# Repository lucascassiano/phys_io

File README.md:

# phys_io
Opensource Low cost hand|finger tracking device for HCIs and Physiotherapy applications

## Possible ICs
### Capacitive Touch/Proximity ICs
- MPR121 - 12Channel w/ I2C interf - https://www.adafruit.com/product/1982

### Power Supply

- TP4056 - LiPo Charger - https://www.sparkfun.com/products/10217

- UA78M33 - 3.3v Regulator

### Micro Controller

- ATMega32u4 - (maybe it's too much for a simple application)

- Attiny44 

## Software - API / Viz tool

- Node.js 
- Babylon.js
- Unity (?)

## Components to buy - April 2017
| Component     | Price (US$) |Quantity| link
| ------------- |:------:|:-----:| --------- |
| TP4056 Battery Charge |  1.65  | 10 | [dx](http://www.dx.com/p/tp4056-4-2w-1-2a-5v-lithium-battery-charging-discharging-protection-module-w-micro-usb-blue-397213#.WOpxGlLlQU4)|
| MPR121 Breakout I2C   |  4.99  | 10 | [dx](http://www.dx.com/p/mpr121-breakout-i2c-capacitive-touch-sensor-controller-module-for-arduino-raspberry-pi-382663#.WOpyglLlSAw)|
| Arduino Micro Pro     |  5.99  | 10 | [dx](http://www.dx.com/p/open-smart-atmega32u4-development-board-pro-micro-for-arduino-452853#.WOpy3lLlSAw)|
| HC-06 Bluetooth Module|  5.99  | 10 | [dx](http://www.dx.com/p/hc-06-serial-port-passthrough-wireless-slave-transceiver-bluetooth-module-for-arduino-382686#.WOpzOFLlSAw)|
| 5x lipo Battery 800mAh|  13.65 | 2  | [dx](http://www.dx.com/p/hj-5pcs-3-7v-800mah-batteries-for-dfd-f163-rc-quadcopter-spare-parts-458005#.WOpzklLlSAw)|
| 10x switch            |  1.92  | 2  | [dx](http://www.dx.com/p/jtron-6-pin-toggle-switch-battery-box-dedicated-switch-black-10-pcs-392709#.WOpz1VLlQU4)|
| 10x Vibration Motor   |  5.89  | 3  | [dx](http://www.dx.com/p/1027-vibration-motor-10x2-7mm-button-type-vibrating-motors-10-pcs-460845#.WOpz-1LlQU4)|

## References Readings 
### Books

[1] http://www.capsense.com/capsense-wp.pdf

[2] Larry K. Baxter Capacitive Sensors Book http://ieeexplore.ieee.org/xpl/mostRecentIssue.jsp?punumber=5264832

[3] Prof. Joseph Paradiso Class 2016 - https://dspace.mit.edu/handle/1721.1/69824

### Papers/Projects (usually that I saw on MIT_MAS.836 class)

[1] 2D printed capacitive/resistive sensors https://dam-prod.media.mit.edu/x/files/thesis/2013/nanwei-phd.pdf

[2] Mathews Radio-Baton https://www.engadget.com/2014/02/02/max-mathews-one-man-electronic-orchestra/

[3] Resistive/Capacitive Charge Division circuit http://ieeexplore.ieee.org/stamp/stamp.jsp?arnumber=1134315

[4] http://resenv.media.mit.edu/#Projects#emgrie:-ergonomic-microgesture-recognition-and-interaction-evaluation

[5] http://nailo.media.mit.edu

### Other Repositories

[1] DIY SmartWatch https://github.com/laubed/diy-smartwatch

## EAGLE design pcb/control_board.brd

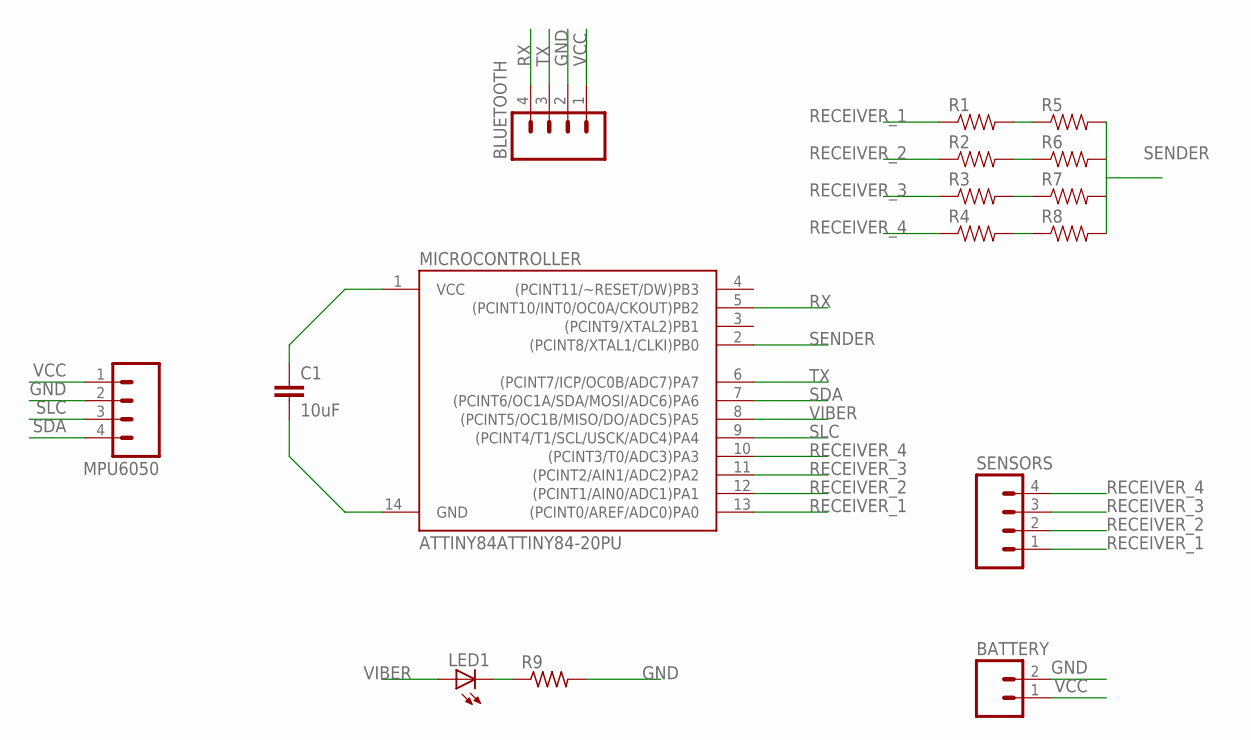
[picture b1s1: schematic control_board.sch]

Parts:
BATTERY: M02POLAR_LOCK; MOLEX-1X2_LOCK
BLUETOOTH: M04PTH; 1X04
C1: 10uF; CAP-PTH-SMALL2
LED1: LED5MM
MICROCONTROLLER: ATTINY84ATTINY84-20PU; DIL14
MPU6050: M04PTH; 1X04
R1, R2, R3, R4, R5, R6, R7, R8: RESISTOREZ; AXIAL-0.3EZ
R9: R-US_0207/10; 0207/10
SENSORS: M04PTH; 1X04

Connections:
GND: BATTERY.2, BLUETOOTH.2, C1.2, MICROCONTROLLER.14 (GND), MPU6050.2, R9.2
unnamed: R2.P$2 (2), R6.P$1 (1)
unnamed: R3.P$2 (2), R7.P$1 (1)
unnamed: R1.P$2 (2), R5.P$1 (1)
unnamed: R4.P$2 (2), R8.P$1 (1)
unnamed: LED1.K (C), R9.1
RECEIVER_1: MICROCONTROLLER.13 ((PCINT0/AREF/ADC0)PA0), R1.P$1 (1), SENSORS.1
RECEIVER_2: MICROCONTROLLER.12 ((PCINT1/AIN0/ADC1)PA1), R2.P$1 (1), SENSORS.2
RECEIVER_3: MICROCONTROLLER.11 ((PCINT2/AIN1/ADC2)PA2), R3.P$1 (1), SENSORS.3
RECEIVER_4: MICROCONTROLLER.10 ((PCINT3/T0/ADC3)PA3), R4.P$1 (1), SENSORS.4
RX: BLUETOOTH.4, MICROCONTROLLER.5 ((PCINT10/INT0/OC0A/CKOUT)PB2)
SDA: MICROCONTROLLER.7 ((PCINT6/OC1A/SDA/MOSI/ADC6)PA6), MPU6050.4
SENDER: MICROCONTROLLER.2 ((PCINT8/XTAL1/CLKI)PB0), R5.P$2 (2), R6.P$2 (2), R7.P$2 (2), R8.P$2 (2)
SLC: MICROCONTROLLER.9 ((PCINT4/T1/SCL/USCK/ADC4)PA4), MPU6050.3
TX: BLUETOOTH.3, MICROCONTROLLER.6 ((PCINT7/ICP/OC0B/ADC7)PA7)
VCC: BATTERY.1, BLUETOOTH.1, C1.1, MICROCONTROLLER.1 (VCC), MPU6050.1
VIBER: LED1.A, MICROCONTROLLER.8 ((PCINT5/OC1B/MISO/DO/ADC5)PA5)

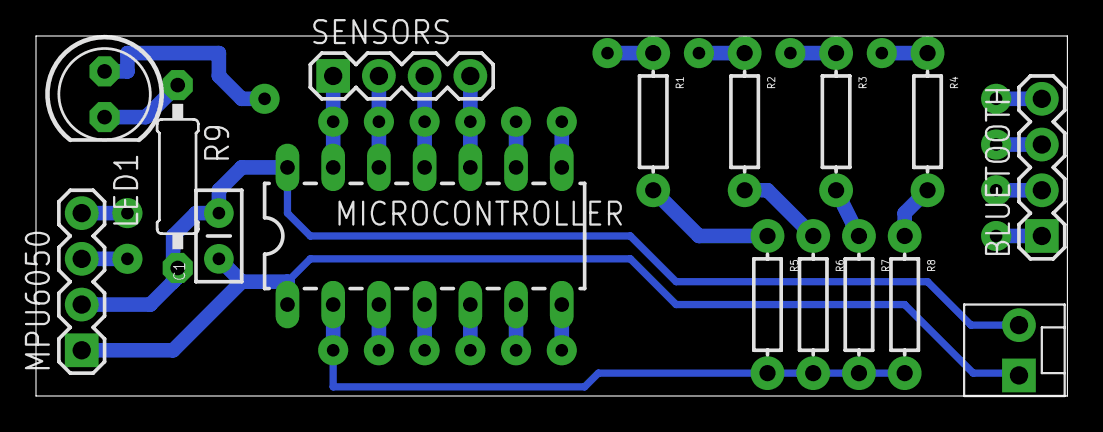
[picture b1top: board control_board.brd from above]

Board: 2 copper layers, 57.3 x 20.0 mm, 16 parts (0 on the bottom side), 17 nets.

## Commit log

2017-04-09 3rd party pcbs added
2017-04-09 mpr121 breakout
2017-04-09 Old pcbs added
2017-04-09 updated on readme
2017-04-09 marktown fix

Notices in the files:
parts and their libraries:
SparkFun-Connectors: Licensing: Creative Commons ShareAlike 4.0 International - https://creativecommons.org/licenses/by-sa/4.0
